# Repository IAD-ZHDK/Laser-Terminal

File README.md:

# Laser-Terminal
This repo contains code an schematics for the laser terminal at ZHdK

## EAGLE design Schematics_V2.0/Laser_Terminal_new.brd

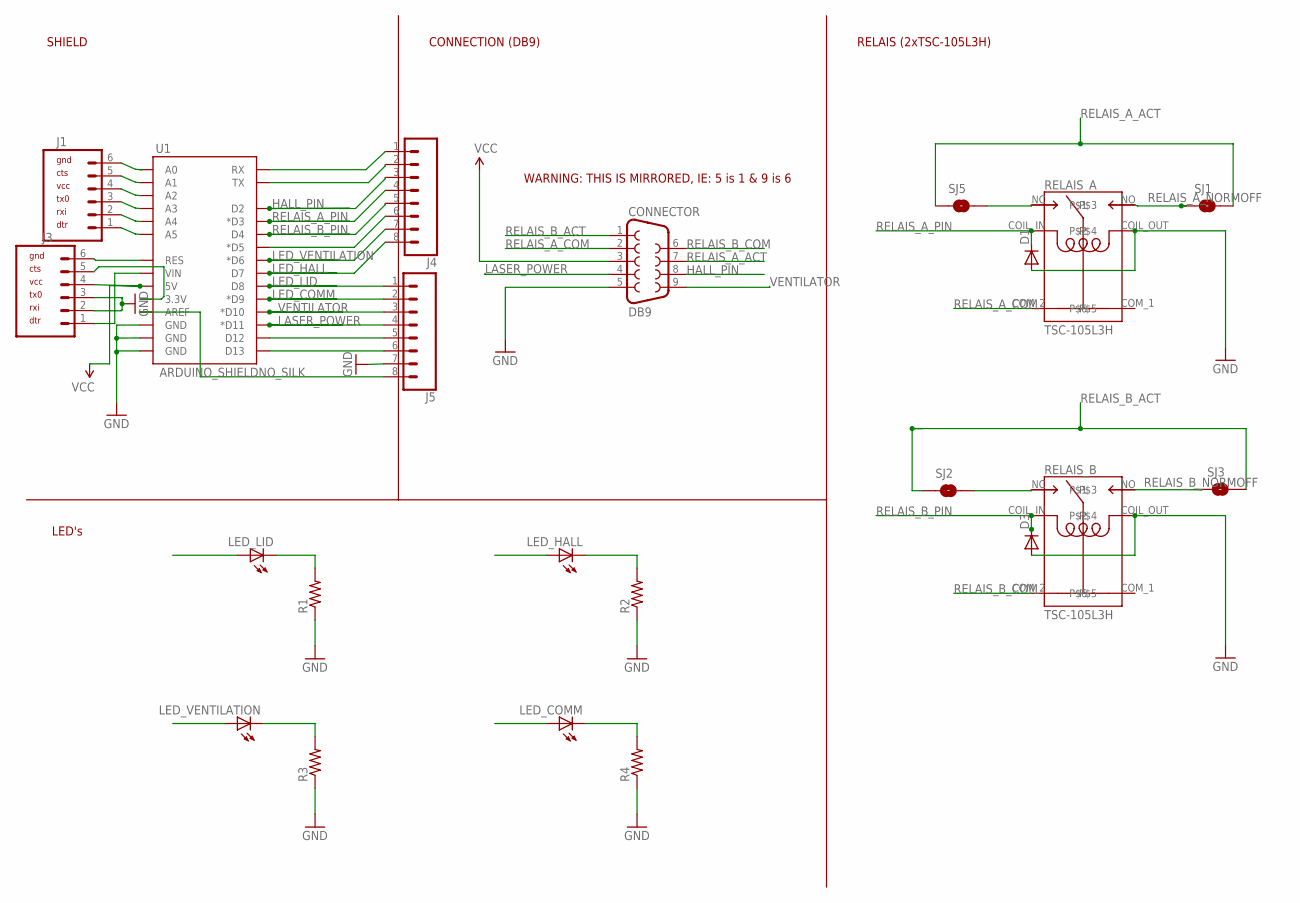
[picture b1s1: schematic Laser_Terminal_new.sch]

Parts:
CONNECTOR: DB9; DB9_MALE
D1, D3: DIODEPTH; DIODE-1N4001
J1, J3: M06NO_SILK_YES_STOP; 1X06_NO_SILK_YES_STOP
J4, J5: CONN_08"; 1X08
LED_COMM: LED5MM
LED_HALL: LED5MM
LED_LID: LED5MM
LED_VENTILATION: LED5MM
R1, R2, R3, R4: RESISTORAXIAL-0.3; AXIAL-0.3
RELAIS_A: TSC-105L3H; TSC_112L3H
RELAIS_B: TSC-105L3H; TSC_112L3H
SJ1, SJ2, SJ5: SOLDERJUMPERNO; SJ_2S-NO
SJ3: JUMPER-SMT_2_NO_SILK; SMT-JUMPER_2_NO_SILK
U1: ARDUINO_SHIELDNO_SILK; DUEMILANOVE_VIAS

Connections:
GND: CONNECTOR.5, D1.A, D3.A, J3.2, J3.3, J5.7, R1.P$1 (1), R2.P$1 (1), R3.P$1 (1), R4.P$1 (1), RELAIS_A.COIL_OUT, RELAIS_B.COIL_OUT, U1.GND@0 (GND), U1.GND@1 (GND), U1.GND@2 (GND)
HALL_PIN: CONNECTOR.8, J4.3, U1.D2
LASER_POWER: CONNECTOR.4, J5.4, U1.D11 (*D11)
LED_COMM: J5.2, LED_COMM.A, U1.D9 (*D9)
LED_HALL: J4.8, LED_HALL.A, U1.D7
LED_LID: J5.1, LED_LID.A, U1.D8
LED_VENTILATION: J4.7, LED_VENTILATION.A, U1.D6 (*D6)
unnamed: RELAIS_B.NC, SJ2.2
unnamed: J1.6, U1.A0
unnamed: J1.5, U1.A1
unnamed: J1.4, U1.A2
unnamed: J1.3, U1.A3
unnamed: LED_LID.K (C), R1.P$2 (2)
unnamed: LED_HALL.K (C), R2.P$2 (2)
unnamed: LED_VENTILATION.K (C), R3.P$2 (2)
unnamed: LED_COMM.K (C), R4.P$2 (2)
unnamed: J1.2, U1.A4
unnamed: J1.1, U1.A5
unnamed: J5.5, U1.D12
unnamed: J5.6, U1.D13
unnamed: RELAIS_A.NC, SJ5.2
unnamed: J3.1, U1.VIN
unnamed: J3.5, U1.3.3V
unnamed: J3.6, U1.RES
unnamed: J4.1, U1.RX
unnamed: J4.2, U1.TX
unnamed: J4.6, U1.D5 (*D5)
unnamed: J5.8, U1.AREF
RELAIS_A_ACT: CONNECTOR.7, SJ1.2, SJ5.1
RELAIS_A_COM: CONNECTOR.2, RELAIS_A.COM_2
RELAIS_A_NORMOFF: RELAIS_A.NO, SJ1.1
RELAIS_A_PIN: D1.C, J4.4, RELAIS_A.COIL_IN, U1.D3 (*D3)
RELAIS_B_ACT: CONNECTOR.1, SJ2.1, SJ3.2
RELAIS_B_COM: CONNECTOR.6, RELAIS_B.COM_2
RELAIS_B_NORMOFF: RELAIS_B.NO, SJ3.1
RELAIS_B_PIN: D3.C, J4.5, RELAIS_B.COIL_IN, U1.D4
VCC: CONNECTOR.3, J3.4, U1.5V
VENTILATOR: CONNECTOR.9, J5.3, U1.D10 (*D10)

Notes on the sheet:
SHIELD
CONNECTION (DB9)
RELAIS (2xTSC-105L3H)
LED's
WARNING: THIS IS MIRRORED, IE: 5 is 1 & 9 is 6

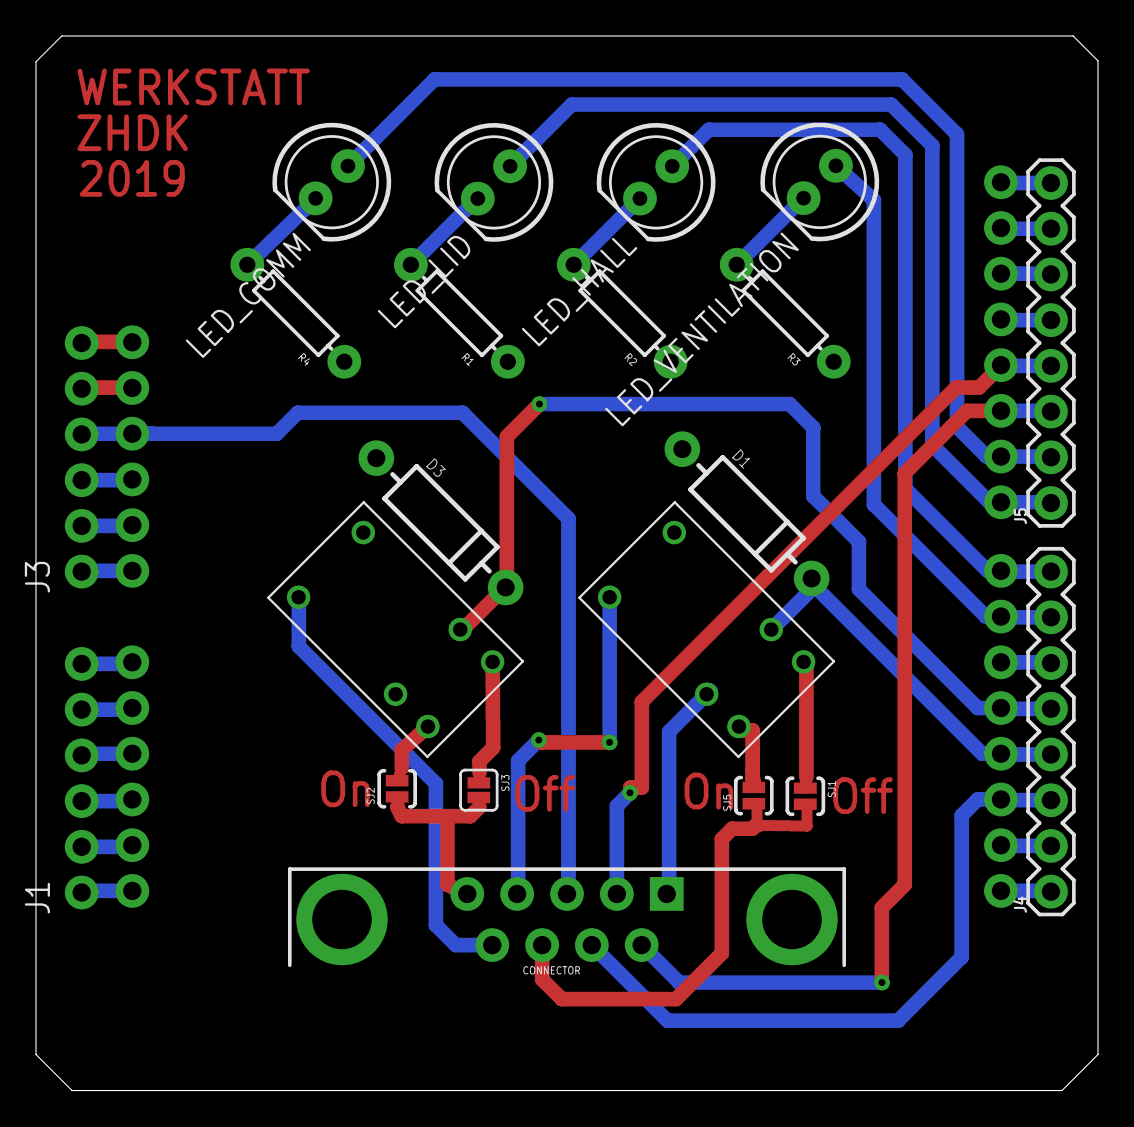
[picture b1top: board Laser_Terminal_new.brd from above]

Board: 2 copper layers, 59.0 x 58.6 mm, 22 parts (0 on the bottom side), 38 nets.

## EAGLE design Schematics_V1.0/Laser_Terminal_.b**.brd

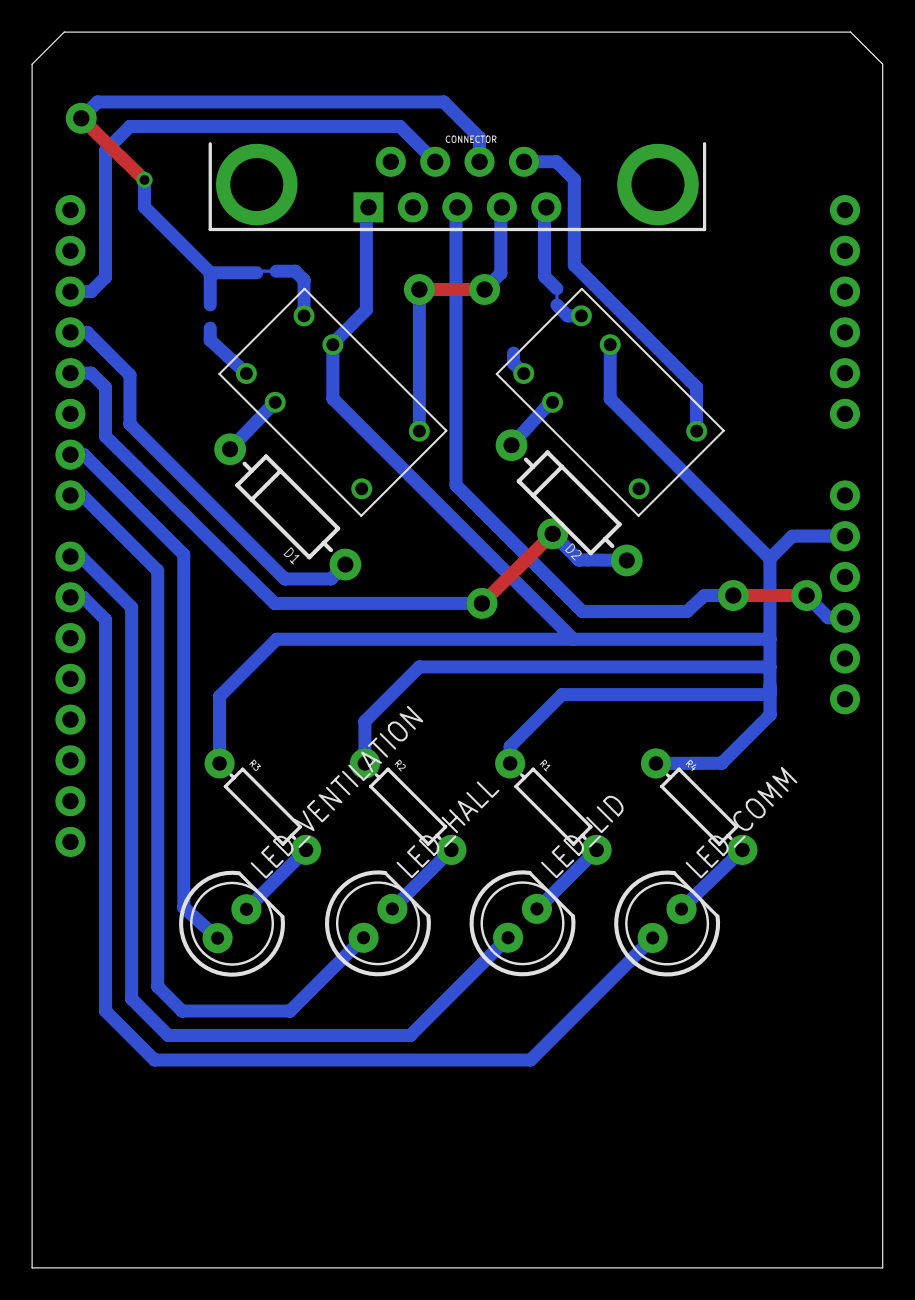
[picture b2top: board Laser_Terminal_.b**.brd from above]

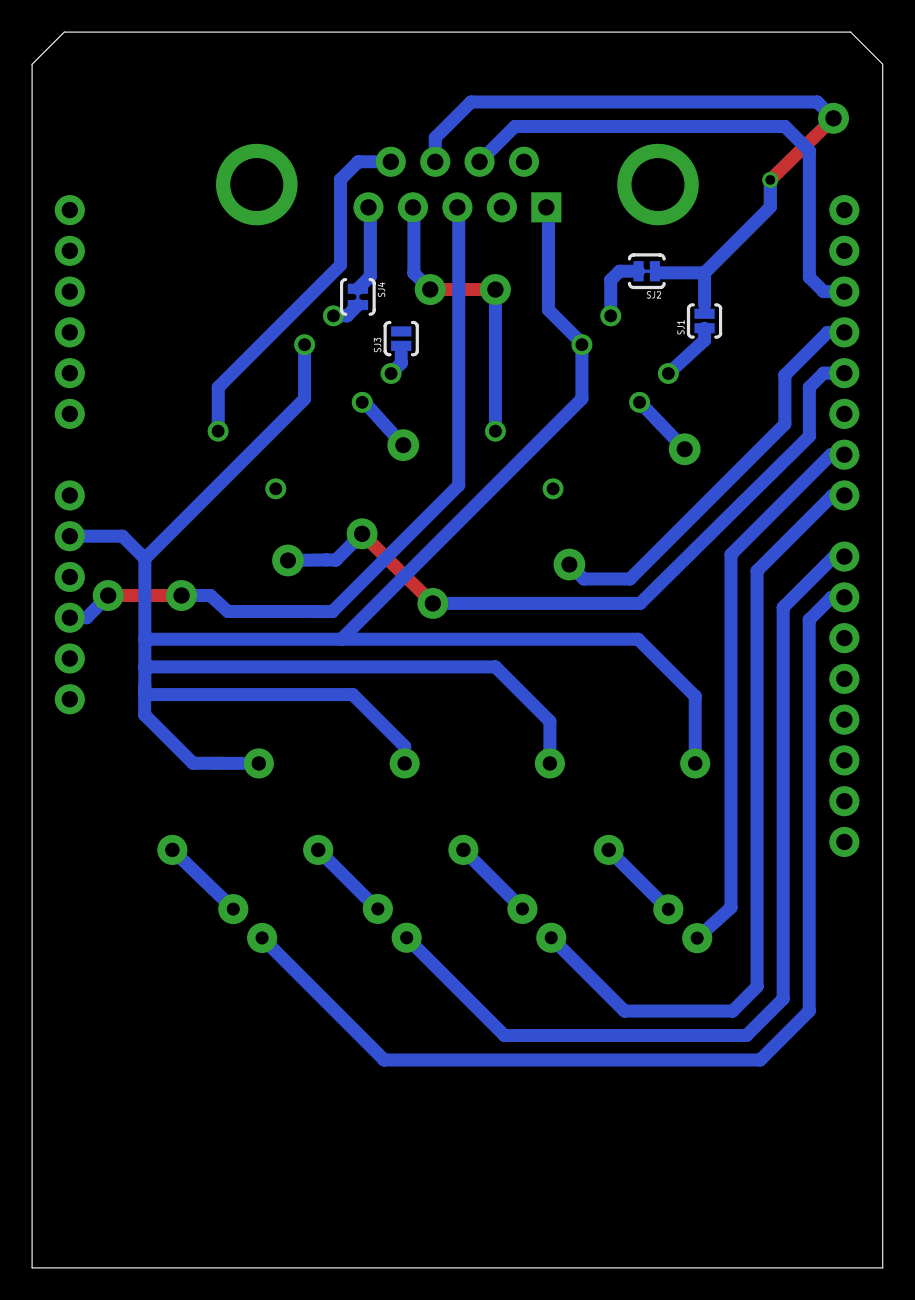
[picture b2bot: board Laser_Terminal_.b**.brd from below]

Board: 2 copper layers, 53.0 x 77.0 mm, 18 parts (4 on the bottom side), 23 nets.

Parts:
CONNECTOR: DB9; DB9_MALE
D1, D2: DIODE-1N4001
LED_COMM: LED5MM
LED_HALL: LED5MM
LED_LID: LED5MM
LED_VENTILATION: LED5MM
R1, R2, R3, R4: AXIAL-0.3
RELAIS_A: TSC-105L3H; TSC_112L3H
RELAIS_B: TSC-105L3H; TSC_112L3H
SJ1, SJ3: SOLDERJUMPERNO; SJ_2S-NO
SJ2, SJ4: SOLDERJUMPERTRACE; SJ_2S-TRACE
U1: ARDUINO_SHIELDNO_SILK; DUEMILANOVE_VIAS

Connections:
GND: CONNECTOR.5, R1.P$1, R2.P$1, R3.P$1, R4.P$1, RELAIS_A.COIL_OUT, RELAIS_B.COIL_OUT, U1.GND@1
HALL_PIN: CONNECTOR.8, U1.D2
LED_COMM: LED_COMM.A, U1.D9
LED_HALL: LED_HALL.A, U1.D7
LED_LID: LED_LID.A, U1.D8
LED_VENTILATION: LED_VENTILATION.A, U1.D6
unnamed: D1.C, RELAIS_A.COIL_IN
unnamed: D2.C, RELAIS_B.COIL_IN
unnamed: LED_LID.K, R1.P$2
unnamed: LED_HALL.K, R2.P$2
unnamed: LED_VENTILATION.K, R3.P$2
unnamed: LED_COMM.K, R4.P$2
RELAIS_A_ACT: CONNECTOR.7, SJ1.2, SJ2.1
RELAIS_A_COM: CONNECTOR.2, RELAIS_A.COM_2
RELAIS_A_NORMOFF: RELAIS_A.NO, SJ1.1
RELAIS_A_NORMON: RELAIS_A.NC, SJ2.2
RELAIS_A_PIN: D1.A, U1.D3
RELAIS_B_ACT: CONNECTOR.1, SJ3.2, SJ4.1
RELAIS_B_COM: CONNECTOR.6, RELAIS_B.COM_2
RELAIS_B_NORMOFF: RELAIS_B.NO, SJ3.1
RELAIS_B_NORMON: RELAIS_B.NC, SJ4.2
RELAIS_B_PIN: D2.A, U1.D4
VCC: CONNECTOR.3, U1.5V

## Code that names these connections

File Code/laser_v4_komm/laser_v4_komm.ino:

//Bibliothek serialComLib
#include "serialComLib.h"

//cmdId constants
#define  CMD_WRITE_DOUT    1
#define  CMD_READ_DIN      2
#define  BUFFER_LENGTH     32

//Vars für serielle Kommunikation
SerialComLib   comLib;
unsigned char  bufferLength;
unsigned char  serialBuffer[BUFFER_LENGTH];
unsigned char  cmdId;

//Vars für digitale Pins: Hall, 2x Relais
int hallPin = 2;
int relaisAPin = 3; // Laser Freischalten 
int relaisBPin = 4; // Ventilator

int DigOut1 = 10; // ventilator power    
int DigOut2 = 11; // laser power 


//Vars für die LEDs
int led_COMM = 9;
int led_LID = 8;
int led_HALL = 7;
int led_VENT = 6;

//Schalter zum Bedienen des Relais (wird später vom Wert aus der DB übernommen)
int schalterIn = 7;
int schalterON;

//Vars für Bauteile
int hallSensor;
boolean relaisAOutput;
boolean relaisBOutput;

//Kontostand (wird aus DB gelesen, vielleicht besser boolean?)
char kontostand;

void setup()
{
  pinMode(hallPin, INPUT);
  pinMode(relaisAPin, OUTPUT);
  pinMode(relaisBPin, OUTPUT);
  pinMode(schalterIn, INPUT);

  pinMode(DigOut1, OUTPUT);
  pinMode(DigOut2, OUTPUT);

  pinMode(led_COMM, OUTPUT);
  pinMode(led_LID, OUTPUT);
  pinMode(led_HALL, OUTPUT);
  pinMode(led_VENT, OUTPUT);

  //Internet Pull-Up Widerstand
  digitalWrite(hallPin, HIGH);

  //Lib öffnen
  comLib.open();
}

void loop()
{
  //Werte lesen, wenn Daten auf dem Serialport sind
  hallSensor = digitalRead(hallPin);
  schalterON = digitalRead(schalterIn);

  //Ventilator EIN, wenn Nullpunkt verlassen, sonst AUS
  if (hallSensor > 0)
  {

    digitalWrite(DigOut1, HIGH); // vent on
    digitalWrite(relaisBPin, HIGH);
    digitalWrite(led_VENT, HIGH);
    digitalWrite(led_HALL, HIGH);
  }
  else
  {
    digitalWrite(DigOut1, LOW); // vent off
    digitalWrite(relaisBPin, LOW);
    digitalWrite(led_VENT, LOW);
    digitalWrite(led_HALL, LOW);
  }

  if (comLib.available())
  {

    //Daten von Serialport lesen
    if (comLib.readCmd(&cmdId, &bufferLength, serialBuffer, BUFFER_LENGTH) != SerialComLib::Ok)
      return;

    switch (cmdId)
    {
      case CMD_WRITE_DOUT:
        digitalWrite(led_COMM, HIGH);

        switch (serialBuffer[0])
        {
          case 0:
            //Signal an Relais A
            digitalWrite(relaisAPin, serialBuffer[1]);
            digitalWrite(led_LID, serialBuffer[1]);
            digitalWrite(DigOut2, serialBuffer[1]); // laser power on/off
            break;
          case 1:
          default:
            //Signal an Relais B
            digitalWrite(relaisBPin, serialBuffer[1]);
            digitalWrite(led_VENT, serialBuffer[1]);
            digitalWrite(DigOut1, serialBuffer[1]); // Vent power on/off
            break;
        }
        break;

      case CMD_READ_DIN:
        digitalWrite(led_COMM, HIGH);

        //Auslesen, was Hallsensor angibt (Laserkopf an Nullpunkt)
        if (hallSensor == 0)
        {
          //Kommunikation mit Python, Laser ist am Nullpunkt
          serialBuffer[0] = 1;
          digitalWrite(led_HALL, HIGH);
        }
        else
        {
          //Kommunikation mit Python, Laser ist unterwegs
          serialBuffer[0] = 0;
          digitalWrite(led_HALL, LOW);
        }
        // send the command packet over serial
        bufferLength = 1;

        // write
        comLib.writeCmd(CMD_READ_DIN, bufferLength, serialBuffer);
        break;
    }
  }
  else
  {
    digitalWrite(led_COMM, LOW);
  }
}

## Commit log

2017-12-29 Initial Commit
    go
2018-03-21 New code for fusion laser, with HAL sensor inverted
2018-03-22 replaced wiring.H with Arduino.h
2018-07-17 Update for new laser power and ventilation System
2018-07-18 Updates for LOGO! power controller and folder renamed for Epilog and Fusion lasers
2018-07-19 Updates for LOGO! system
2018-12-20 Add New PCB
2019-04-09 New Board Design
2019-04-09 Folders renamed
2019-07-17 Updates to Epson Plotter
2019-07-19 Merged Risograph into terminal repo
2019-07-19 Updated for Zund_Plotter
2019-08-27 Update Risograph for new digital sensor.
2019-08-27 Timmer update for OSX
2019-10-02 Minor Changes

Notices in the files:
parts and their libraries:
SparkFun-Connectors: Licensing: Creative Commons ShareAlike 4.0 International - https://creativecommons.org/licenses/by-sa/4.0
